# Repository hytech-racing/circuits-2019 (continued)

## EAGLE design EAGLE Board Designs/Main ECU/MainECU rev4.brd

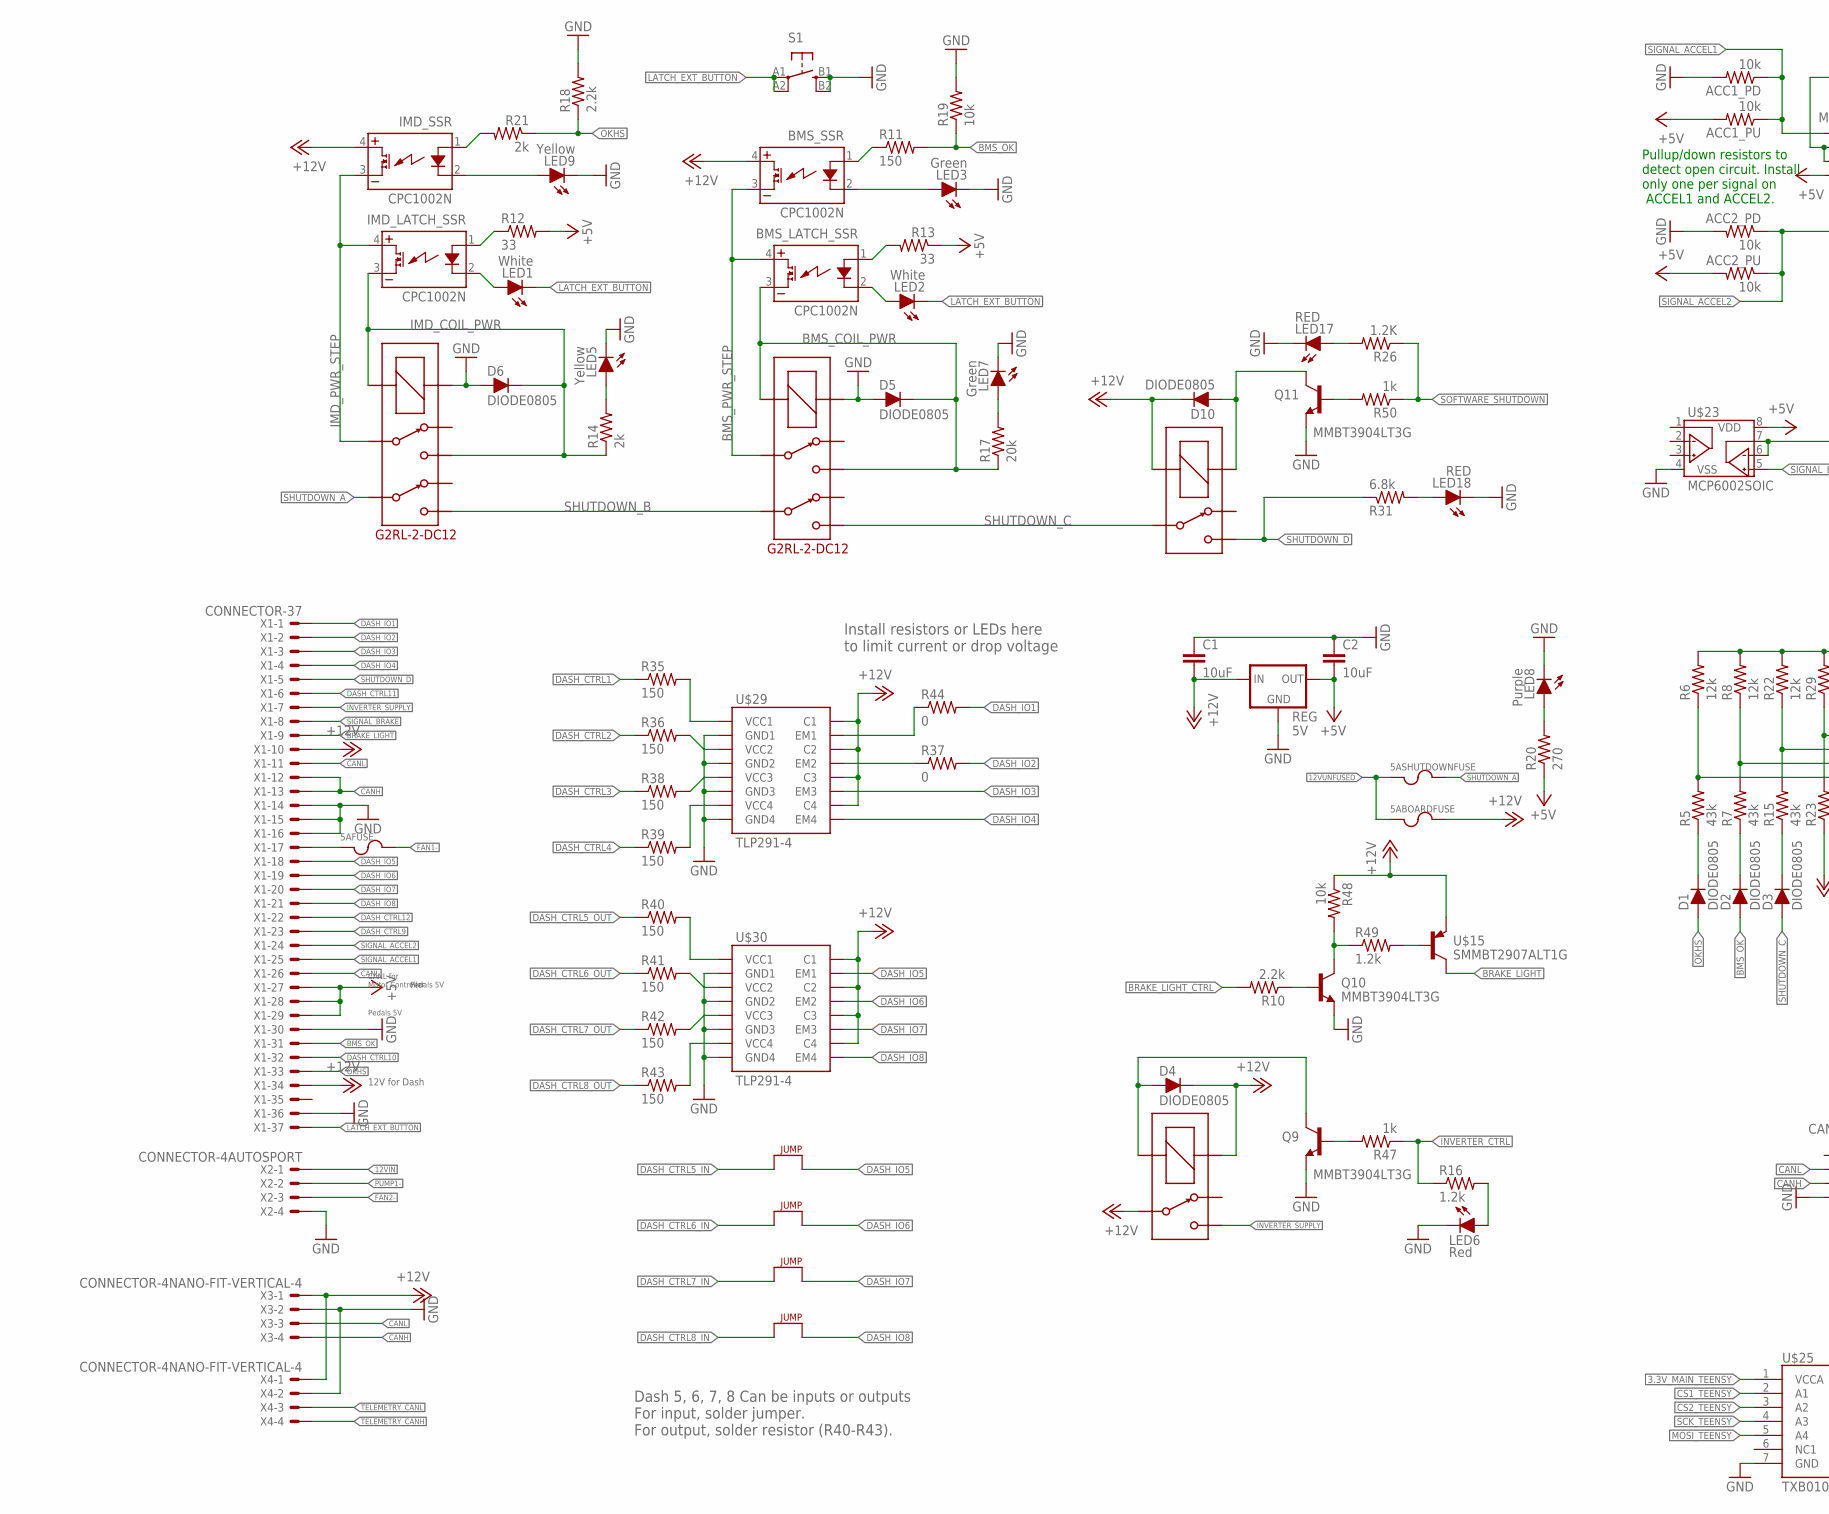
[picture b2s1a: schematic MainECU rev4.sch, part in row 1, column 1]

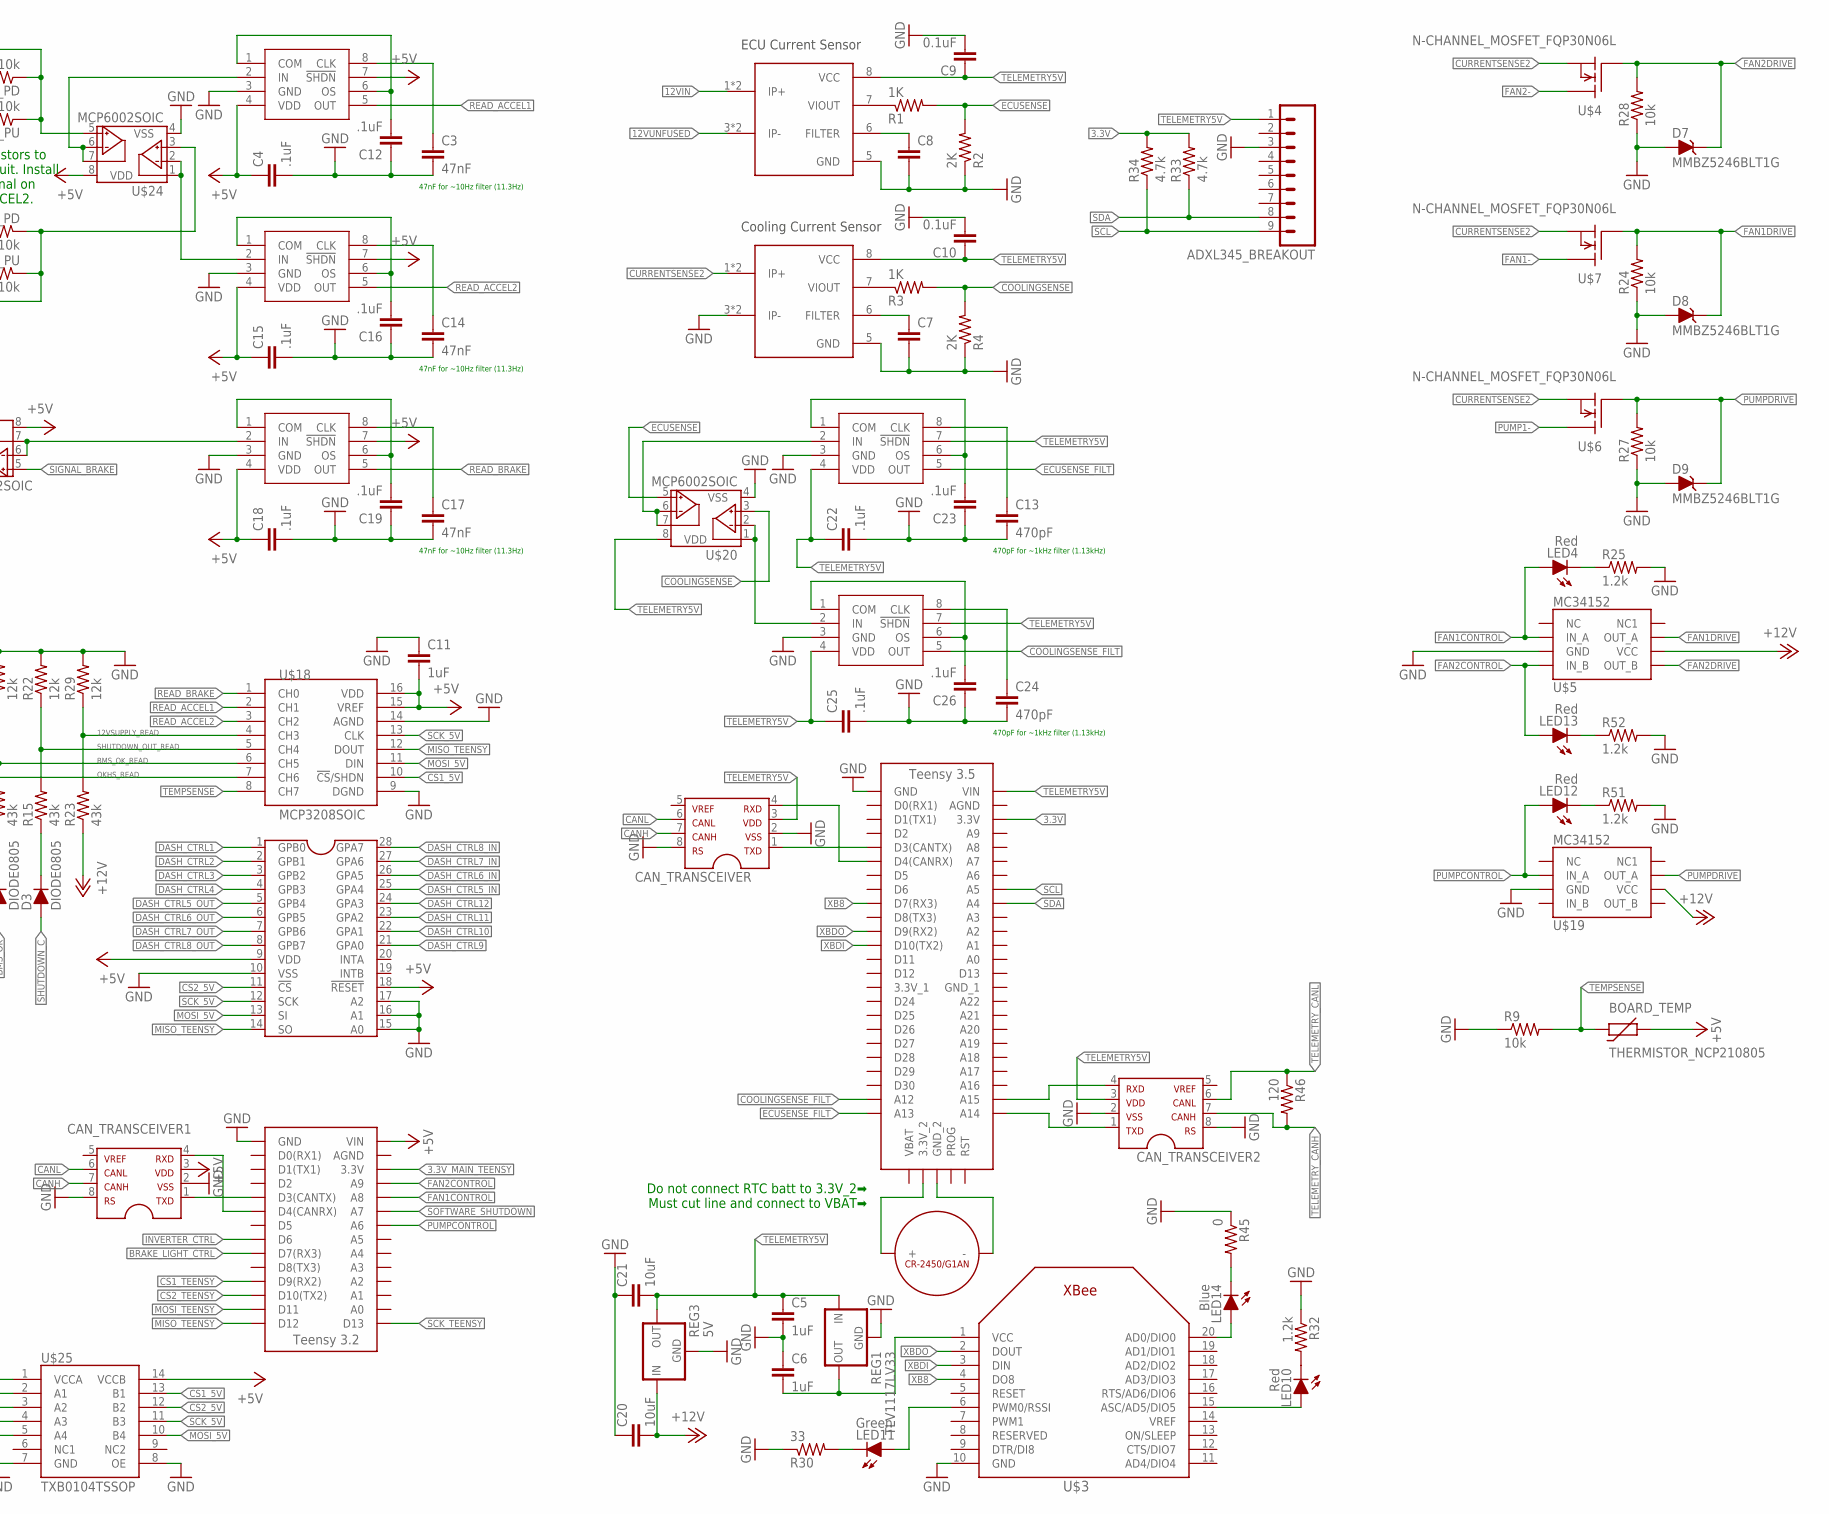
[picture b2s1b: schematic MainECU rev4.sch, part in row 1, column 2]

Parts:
5ABOARDFUSE, 5AFUSE, 5ASHUTDOWNFUSE: FUSE_MINIBLADE; MINI-BLADE_FUSE_HOLDER
ACC1_PD, ACC1_PU, ACC2_PD, ACC2_PU: 10k; 0805
ADXL345_BREAKOUT: M09; 1X09
BMS_LATCH_SSR: CPC1002N; SOP04
BMS_SSR: CPC1002N; SOP04
BOARD_TEMP: THERMISTOR_NCP210805; 0805
C1, C2, C20, C21: 10uF; 0805
C3, C14, C17: 47nF; 0805
C4, C12, C15, C16, C18, C19, C22, C23, C25, C26: .1uF; 0805
C5, C6, C11: 1uF; 0805
C7, C8: CAP0805; 0805
C9, C10: 0.1uF; 0805
C13, C24: 470pF; 0805
CAN_TRANSCEIVER, CAN_TRANSCEIVER1, CAN_TRANSCEIVER2: MCP2551; SOIC-08
D1, D2, D3, D4, D5, D6, D10: DIODE0805; 0805_D
D7, D8, D9: MMBZ5246BLT1G; SOT23
IMD_LATCH_SSR: CPC1002N; SOP04
IMD_SHUTDOWN, IMD_SHUTDOWN1: G2RL-2-DC12; G2RL-2
IMD_SSR: CPC1002N; SOP04
LED1, LED2: White; LED-805
LED3, LED7, LED11: Green; LED-805
LED4, LED6, LED10, LED12, LED13: Red; LED-805
LED5, LED9: Yellow; LED-805
LED8: Purple; LED-805
LED14: Blue; LED-805
LED17, LED18: RED; LED-805
Q9, Q10, Q11: MMBT3904LT3G; SOT23
R1, R3: 1K; 0805
R2, R4: 2K; 0805
R5, R7, R15, R23: 43k; 0805
R6, R8, R22, R29: 12k; 0805
R9, R19, R24, R27, R28, R48: 10k; 0805
R10, R18: 2.2k; 0805
R11, R35, R36, R38, R39, R40, R41, R42, R43: 150; 0805
R12, R13, R30: 33; 0805
R14, R21: 2k; 0805
R16, R25, R32, R49, R51, R52: 1.2k; 0805
R17: 20k; 0805
R20: 270; 0805
R26: 1.2K; 0805
R31: 6.8k; 0805
R33, R34: 4.7k; 0805
R37, R44, R45: 0; 0805
R46: 120; 0805
R47, R50: 1k; 0805
REG, REG3: 5V; OKI-78SR
REG1: TLV1117LV33; SOT223
S1: BTN_10-XXSMD; TACTILE_SWITCH_SMD_6.2MM_TALL
SOFTWARE_SHUTOFF: G5LE; ZF112
U$1: TEENSY_3.2_SIMPLE
U$2: TEENSY_3.5_EXT
U$3: XBEE
U$4, U$6, U$7: N-CHANNEL_MOSFET_FQP30N06L; TO-220-H-HOLE
U$5, U$19: MC34152; SOIC-08
U$8: G5LE; ZF112
U$9, U$10: ACS715_CURRENT_SENSOR; SOP8
U$11, U$12, U$13, U$14: JUMPER; 0805
U$15: SMMBT2907ALT1G; SOT23
U$16: CR-2450/G1AN
U$17: MCP23S17SSOP28; SSOP28
U$18: MCP3208SOIC; SOIC-16
U$20, U$23, U$24: MCP6002SOIC; SOIC-08
U$21, U$22, U$26, U$27, U$28: MAX7480; SOIC-08
U$25: TXB0104TSSOP; TSSOP-14
U$29, U$30: TLP291-4; 11-11F1
X1: CONNECTOR-37; AUTOSPORT_14-35
X2: CONNECTOR-4AUTOSPORT; AUTOSPORT_12-04
X3, X4: CONNECTOR-4NANO-FIT-VERTICAL-4; NANO-FIT_VERTICAL-4

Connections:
3.3V: R33.2, R34.2, U$2.3.3V
3.3V_MAIN_TEENSY: U$1.3.3V, U$25.1 (VCCA)
12VIN: U$9.1 (IP+), U$9.2 (IP+), X2.P$1
12VSUPPLY_READ: R23.2, R29.1, U$18.4 (CH3)
12VUNFUSED: 5ABOARDFUSE.L1 (1), 5ABOARDFUSE.L2 (1), 5ASHUTDOWNFUSE.L1 (1), 5ASHUTDOWNFUSE.L2 (1), U$9.3 (IP-), U$9.4 (IP-)
+5V: ACC1_PU.2, ACC2_PU.2, BOARD_TEMP.1, C2.2, C4.1, C11.2, C15.1, C18.1, CAN_TRANSCEIVER1.3, R12.2, R13.1, R20.1, REG.3 (OUT), U$1.VIN, U$17.9 (VDD), U$17.18 (!RESET), U$18.15 (VREF), U$18.16 (VDD), U$23.8 (VDD), U$24.8 (VDD), U$25.14 (VCCB), U$26.4 (VDD), U$26.7 (!SHDN), U$27.4 (VDD), U$27.7 (!SHDN), U$28.4 (VDD), U$28.7 (!SHDN), X1.P$27, X1.P$28, X1.P$29
+12V: 5ABOARDFUSE.R1 (2), 5ABOARDFUSE.R2 (2), BMS_SSR.4 (DC+), C1.2, C20.2, D4.C, D10.C, IMD_SSR.4 (DC+), R23.1, R48.1, REG.1 (IN), REG3.1 (IN), SOFTWARE_SHUTOFF.2 (COIL-), U$5.6 (VCC), U$8.1 (COIL+), U$8.P, U$15.2 (E), U$19.6 (VCC), U$29.10 (C4), U$29.12 (C3), U$29.14 (C2), U$29.16 (C1), U$30.10 (C4), U$30.12 (C3), U$30.14 (C2), U$30.16 (C1), X1.P$10, X1.P$34, X3.P$1, X4.P$1
BMS_COIL_PWR: BMS_LATCH_SSR.3 (DC-), D5.C, IMD_SHUTDOWN1.4, IMD_SHUTDOWN1.COIL-, R17.1
BMS_OK: D2.A, R11.2, R19.1, X1.P$31
BMS_OK_READ: R7.2, R8.1, U$18.6 (CH5)
BMS_PWR_STEP: BMS_LATCH_SSR.4 (DC+), BMS_SSR.3 (DC-), IMD_SHUTDOWN1.3
BRAKE_LIGHT: U$15.3 (C), X1.P$9
BRAKE_LIGHT_CTRL: R10.2, U$1.D7(RX3)
CANH: CAN_TRANSCEIVER.7, CAN_TRANSCEIVER1.7, X1.P$12, X1.P$13, X3.P$4
CANL: CAN_TRANSCEIVER.6, CAN_TRANSCEIVER1.6, X1.P$11, X1.P$26, X3.P$3
COOLINGSENSE: R3.2, R4.2, U$20.3 (VINA+)
COOLINGSENSE_FILT: U$2.A12, U$22.5 (OUT)
CS1_5V: U$18.10 (!CS!/SHDN), U$25.13 (B1)
CS1_TEENSY: U$1.D9(RX2), U$25.2 (A1)
CS2_5V: U$17.11 (!CS), U$25.12 (B2)
CS2_TEENSY: U$1.D10(TX2), U$25.3 (A2)
CURRENTSENSE2: U$4.3 (S), U$6.3 (S), U$7.3 (S), U$10.1 (IP+), U$10.2 (IP+)
DASH_CTRL1: R35.1, U$17.1 (GPB0)
DASH_CTRL2: R36.1, U$17.2 (GPB1)
DASH_CTRL3: R38.1, U$17.3 (GPB2)
DASH_CTRL4: R39.1, U$17.4 (GPB3)
DASH_CTRL5_IN: U$12.2, U$17.25 (GPA4)
DASH_CTRL5_OUT: R40.1, U$17.5 (GPB4)
DASH_CTRL6_IN: U$11.2, U$17.26 (GPA5)
DASH_CTRL6_OUT: R41.1, U$17.6 (GPB5)
DASH_CTRL7_IN: U$13.2, U$17.27 (GPA6)
DASH_CTRL7_OUT: R42.1, U$17.7 (GPB6)
DASH_CTRL8_IN: U$14.2, U$17.28 (GPA7)
DASH_CTRL8_OUT: R43.1, U$17.8 (GPB7)
DASH_CTRL9: U$17.21 (GPA0), X1.P$23
DASH_CTRL10: U$17.22 (GPA1), X1.P$32
DASH_CTRL11: U$17.23 (GPA2), X1.P$6
DASH_CTRL12: U$17.24 (GPA3), X1.P$22
DASH_IO1: R44.2, X1.P$1
DASH_IO2: R37.2, X1.P$2
DASH_IO3: U$29.11 (EM3), X1.P$3
DASH_IO4: U$29.9 (EM4), X1.P$4
DASH_IO5: U$12.1, U$30.15 (EM1), X1.P$18
DASH_IO6: U$11.1, U$30.13 (EM2), X1.P$19
DASH_IO7: U$13.1, U$30.11 (EM3), X1.P$20
DASH_IO8: U$14.1, U$30.9 (EM4), X1.P$21
ECUSENSE: R1.2, R2.2, U$20.5 (VINB+)
ECUSENSE_FILT: U$2.A13, U$21.5 (OUT)
FAN1-: 5AFUSE.R1 (2), 5AFUSE.R2 (2), U$7.2 (D)
FAN1CONTROL: LED4.A, U$1.A8, U$5.2 (IN_A)
FAN1DRIVE: D8.3 (C), R24.2, U$5.7 (OUT_A), U$7.1 (G)
FAN2-: U$4.2 (D), X2.P$3
FAN2CONTROL: LED13.A, U$1.A9, U$5.4 (IN_B)
FAN2DRIVE: D7.3 (C), R28.2, U$4.1 (G), U$5.5 (OUT_B)
GND: ACC1_PD.2, ACC2_PD.2, ADXL345_BREAKOUT.3, C1.1, C2.1, C3.2, C4.2, C5.2, C6.1, C7.2, C8.2, C9.2, C10.2, C11.1, C12.1, C13.2, C14.2, C15.2, C16.1, C17.2, C18.2, C19.1, C20.1, C21.1, C22.2, C23.1, C24.2, C25.2, C26.1, CAN_TRANSCEIVER.2, CAN_TRANSCEIVER.8, CAN_TRANSCEIVER1.2, CAN_TRANSCEIVER1.8, CAN_TRANSCEIVER2.2, CAN_TRANSCEIVER2.8, D5.A, D6.A, D7.1 (A), D8.1 (A), D9.1 (A), IMD_SHUTDOWN.COIL+, IMD_SHUTDOWN1.COIL+, LED3.C, LED5.C, LED6.C, LED7.C, LED8.C, LED9.C, LED17.C, LED18.C, Q9.2 (EMITTER), Q10.2 (EMITTER), Q11.2 (EMITTER), R2.1, R4.1, R6.2, R8.2, R9.1, R18.2, R19.2, R22.2, R24.1, R25.2, R27.1, R28.1, R29.2, R30.1, R32.1, R45.1, R51.2, R52.2, REG.2 (GND), REG1.1 (GND), REG3.2 (GND), S1.B1 (S), S1.B2 (S1), U$1.GND, U$2.GND, U$3.10 (GND), U$5.3 (GND), U$9.5 (GND), U$10.3 (IP-), U$10.4 (IP-), U$10.5 (GND), U$17.10 (VSS), U$17.15 (A0), U$17.16 (A1), U$17.17 (A2), U$18.9 (DGND), U$18.14 (AGND), U$19.3 (GND), U$20.4 (VSS), U$21.3 (GND), U$22.3 (GND), U$23.4 (VSS), U$24.4 (VSS), U$25.7 (GND), U$25.8 (OE), U$26.3 (GND), U$27.3 (GND), U$28.3 (GND), U$29.2 (GND1), U$29.4 (GND2), U$29.6 (GND3), U$29.8 (GND4), U$30.2 (GND1), U$30.4 (GND2), U$30.6 (GND3), U$30.8 (GND4), X1.P$14, X1.P$15, X1.P$16, X1.P$30, X1.P$36, X2.P$4, X3.P$2, X4.P$2
IMD_COIL_PWR: D6.C, IMD_LATCH_SSR.3 (DC-), IMD_SHUTDOWN.4, IMD_SHUTDOWN.COIL-, R14.1
IMD_PWR_STEP: IMD_LATCH_SSR.4 (DC+), IMD_SHUTDOWN.3, IMD_SSR.3 (DC-)
INVERTER_CTRL: R16.1, R47.1, U$1.D6
INVERTER_SUPPLY: U$8.S, X1.P$7
LATCH_EXT_BUTTON: LED1.C, LED2.C, S1.A1, S1.A2 (P1), X1.P$37
MISO_TEENSY: U$1.D12, U$17.14 (SO), U$18.12 (DOUT)
MOSI_5V: U$17.13 (SI), U$18.11 (DIN), U$25.10 (B4)
MOSI_TEENSY: U$1.D11, U$25.5 (A4)
unnamed: 5AFUSE.L1 (1), 5AFUSE.L2 (1), X1.P$17
unnamed: IMD_LATCH_SSR.2 (CONTROL-), LED1.A
unnamed: R1.1, U$9.7 (VIOUT)
unnamed: C12.2, U$27.1 (COM), U$27.6 (OS)
unnamed: IMD_LATCH_SSR.1 (CONTROL+), R12.1
unnamed: R3.1, U$10.7 (VIOUT)
unnamed: Q10.1 (BASE), R10.1
unnamed: C8.1, U$9.6 (FILTER)
unnamed: BMS_SSR.2 (CONTROL-), LED3.A
unnamed: D1.C, R5.1
unnamed: D2.C, R7.1
unnamed: BMS_LATCH_SSR.1 (CONTROL+), R13.2
unnamed: CAN_TRANSCEIVER.4, U$2.D4(CANRX)
unnamed: CAN_TRANSCEIVER.1, U$2.D3(CANTX)
unnamed: CAN_TRANSCEIVER1.4, U$1.D4(CANRX)
unnamed: BMS_LATCH_SSR.2 (CONTROL-), LED2.A
unnamed: Q10.3 (COLLECTOR), R48.2, R49.1
unnamed: BMS_SSR.1 (CONTROL+), R11.1
unnamed: LED5.A, R14.2
unnamed: U$20.1 (VOUTA), U$20.2 (VINA-), U$22.2 (IN)
unnamed: C3.1, U$27.8 (CLK)
unnamed: CAN_TRANSCEIVER1.1, U$1.D3(CANTX)
unnamed: U$24.1 (VOUTA), U$24.2 (VINA-), U$28.2 (IN)
unnamed: U$24.6 (VINB-), U$24.7 (VOUTB), U$27.2 (IN)
unnamed: U$23.6 (VINB-), U$23.7 (VOUTB), U$26.2 (IN)
unnamed: Q11.1 (BASE), R50.2
unnamed: D10.A, Q11.3 (COLLECTOR), SOFTWARE_SHUTOFF.1 (COIL+)
unnamed: LED6.A, R16.2
unnamed: LED8.A, R20.2
unnamed: R36.2, U$29.3 (VCC2)
unnamed: IMD_SSR.1 (CONTROL+), R21.2
unnamed: LED7.A, R17.2
unnamed: D3.C, R15.1
unnamed: IMD_SSR.2 (CONTROL-), LED9.A
unnamed: LED14.C, R45.2
unnamed: C16.2, U$28.1 (COM), U$28.6 (OS)
unnamed: C19.2, U$26.1 (COM), U$26.6 (OS)
unnamed: C14.1, U$28.8 (CLK)
unnamed: U$20.6 (VINB-), U$20.7 (VOUTB), U$21.2 (IN)
unnamed: LED18.A, R31.2
unnamed: C17.1, U$26.8 (CLK)
unnamed: R37.1, U$29.13 (EM2)
unnamed: C23.2, U$21.1 (COM), U$21.6 (OS)
unnamed: C13.1, U$21.8 (CLK)
unnamed: LED11.C, R30.2
unnamed: LED17.A, R26.2
unnamed: LED11.A, U$3.6 (PWM0/RSSI)
unnamed: C7.1, U$10.6 (FILTER)
unnamed: LED10.A, U$3.15 (ASC/AD5/DIO5)
unnamed: LED10.C, R32.2
unnamed: R35.2, U$29.1 (VCC1)
unnamed: R38.2, U$29.5 (VCC3)
unnamed: R39.2, U$29.7 (VCC4)
unnamed: R40.2, U$30.1 (VCC1)
unnamed: R41.2, U$30.3 (VCC2)
unnamed: R42.2, U$30.5 (VCC3)
unnamed: R43.2, U$30.7 (VCC4)
unnamed: R49.2, U$15.1 (B)
unnamed: R44.1, U$29.15 (EM1)
unnamed: U$2.3.3V_2, U$16.+_0 (+), U$16.+_1 (+)
unnamed: U$2.GND_2, U$16.-
unnamed: CAN_TRANSCEIVER2.4, U$2.A15
unnamed: LED14.A, U$3.20 (AD0/DIO0)
unnamed: CAN_TRANSCEIVER2.1, U$2.A14
unnamed: Q9.1 (BASE), R47.2
unnamed: D4.A, Q9.3 (COLLECTOR), U$8.2 (COIL-)
unnamed: C26.2, U$22.1 (COM), U$22.6 (OS)
unnamed: C24.1, U$22.8 (CLK)
unnamed: LED4.C, R25.1
unnamed: LED12.C, R51.1
unnamed: LED13.C, R52.1
OKHS: D1.A, R18.1, R21.1, X1.P$33
OKHS_READ: R5.2, R6.1, U$18.7 (CH6)
PUMP1-: U$6.2 (D), X2.P$2
PUMPCONTROL: LED12.A, U$1.A6, U$19.2 (IN_A)
PUMPDRIVE: D9.3 (C), R27.2, U$6.1 (G), U$19.7 (OUT_A)
READ_ACCEL1: U$18.2 (CH1), U$27.5 (OUT)
READ_ACCEL2: U$18.3 (CH2), U$28.5 (OUT)
READ_BRAKE: U$18.1 (CH0), U$26.5 (OUT)
SCK_5V: U$17.12 (SCK), U$18.13 (CLK), U$25.11 (B3)
SCK_TEENSY: U$1.D13, U$25.4 (A3)
SCL: ADXL345_BREAKOUT.9, R34.1, U$2.A5
SDA: ADXL345_BREAKOUT.8, R33.1, U$2.A4
SHUTDOWN_A: 5ASHUTDOWNFUSE.R1 (2), 5ASHUTDOWNFUSE.R2 (2), IMD_SHUTDOWN.6
SHUTDOWN_B: IMD_SHUTDOWN.5, IMD_SHUTDOWN1.6
SHUTDOWN_C: D3.A, IMD_SHUTDOWN1.5, SOFTWARE_SHUTOFF.P
SHUTDOWN_D: R31.1, SOFTWARE_SHUTOFF.S, X1.P$5
SHUTDOWN_OUT_READ: R15.2, R22.1, U$18.5 (CH4)
SIGNAL_ACCEL1: ACC1_PD.1, ACC1_PU.1, U$24.5 (VINB+), X1.P$25
SIGNAL_ACCEL2: ACC2_PD.1, ACC2_PU.1, U$24.3 (VINA+), X1.P$24
SIGNAL_BRAKE: U$23.5 (VINB+), X1.P$8
SOFTWARE_SHUTDOWN: R26.1, R50.1, U$1.A7
TELEMETRY5V: ADXL345_BREAKOUT.1, C5.1, C9.1, C10.1, C21.2, C22.1, C25.1, CAN_TRANSCEIVER.3, CAN_TRANSCEIVER2.3, REG1.3 (IN), REG3.3 (OUT), U$2.VIN, U$9.8 (VCC), U$10.8 (VCC), U$20.8 (VDD), U$21.4 (VDD), U$21.7 (!SHDN), U$22.4 (VDD), U$22.7 (!SHDN)
TELEMETRY_CANH: CAN_TRANSCEIVER2.7, R46.2, X4.P$4
TELEMETRY_CANL: CAN_TRANSCEIVER2.6, R46.1, X4.P$3
TEMPSENSE: BOARD_TEMP.2, R9.2, U$18.8 (CH7)
VCC: C6.2, REG1.2 (OUT), REG1.4 (OUT), U$3.1 (VCC)
XB8: U$2.D7(RX3), U$3.4 (DO8)
XBDI: U$2.D10(TX2), U$3.3 (DIN)
XBDO: U$2.D9(RX2), U$3.2 (DOUT)

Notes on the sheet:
ECU Current Sensor
Cooling Current Sensor
Pullup/down resistors to detect open circuit. Install only one per signal on ACCEL1 and ACCEL2.
Pedals 5V
CANL for Motor Controller
47nF for ~10Hz filter (11.3Hz)
12V for Dash
Dash 5, 6, 7, 8 Can be inputs or outputs For input, solder jumper. For output, solder resistor (R40-R43).
470pF for ~1kHz filter (1.13kHz)
Install resistors or LEDs here to limit current or drop voltage
Do not connect RTC batt to 3.3V_2➡ Must cut line and connect to VBAT➡

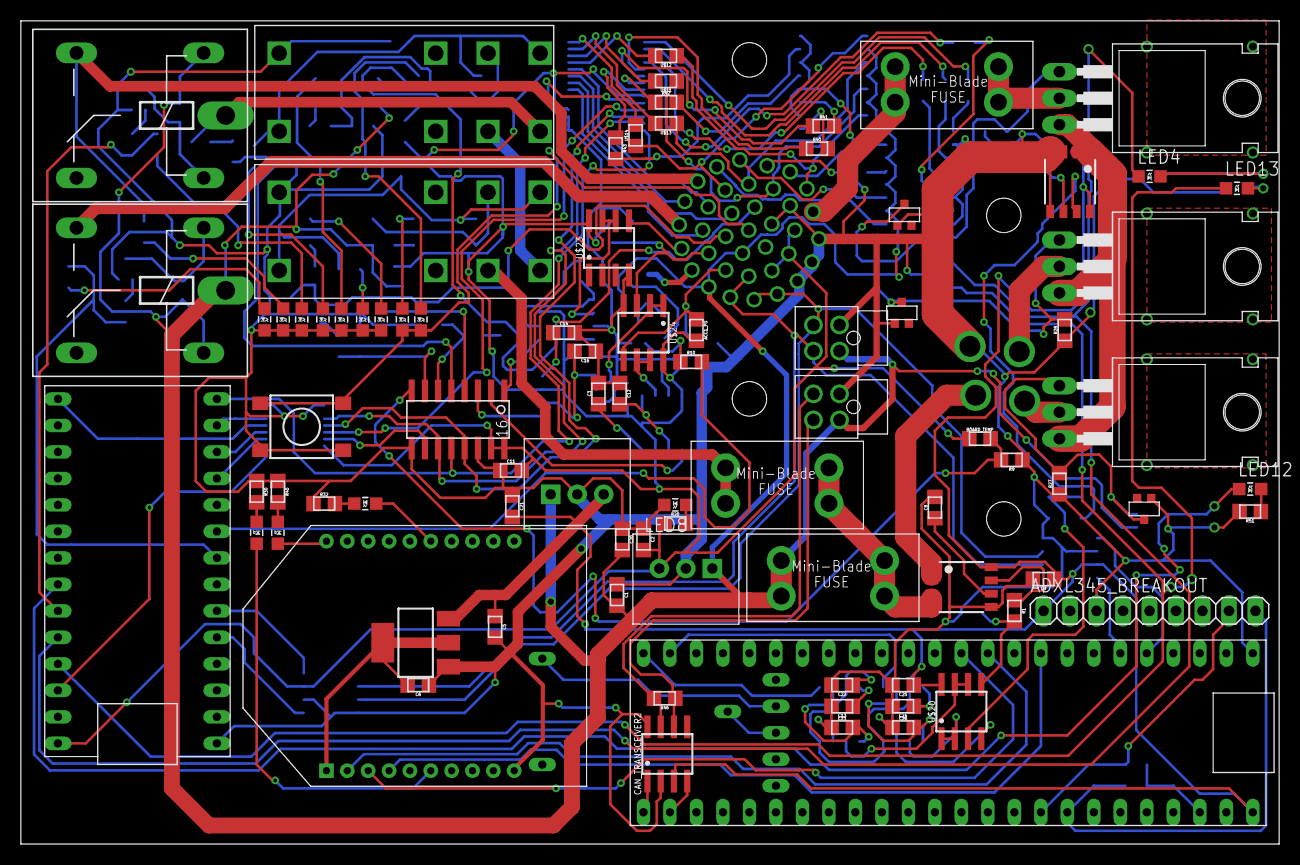
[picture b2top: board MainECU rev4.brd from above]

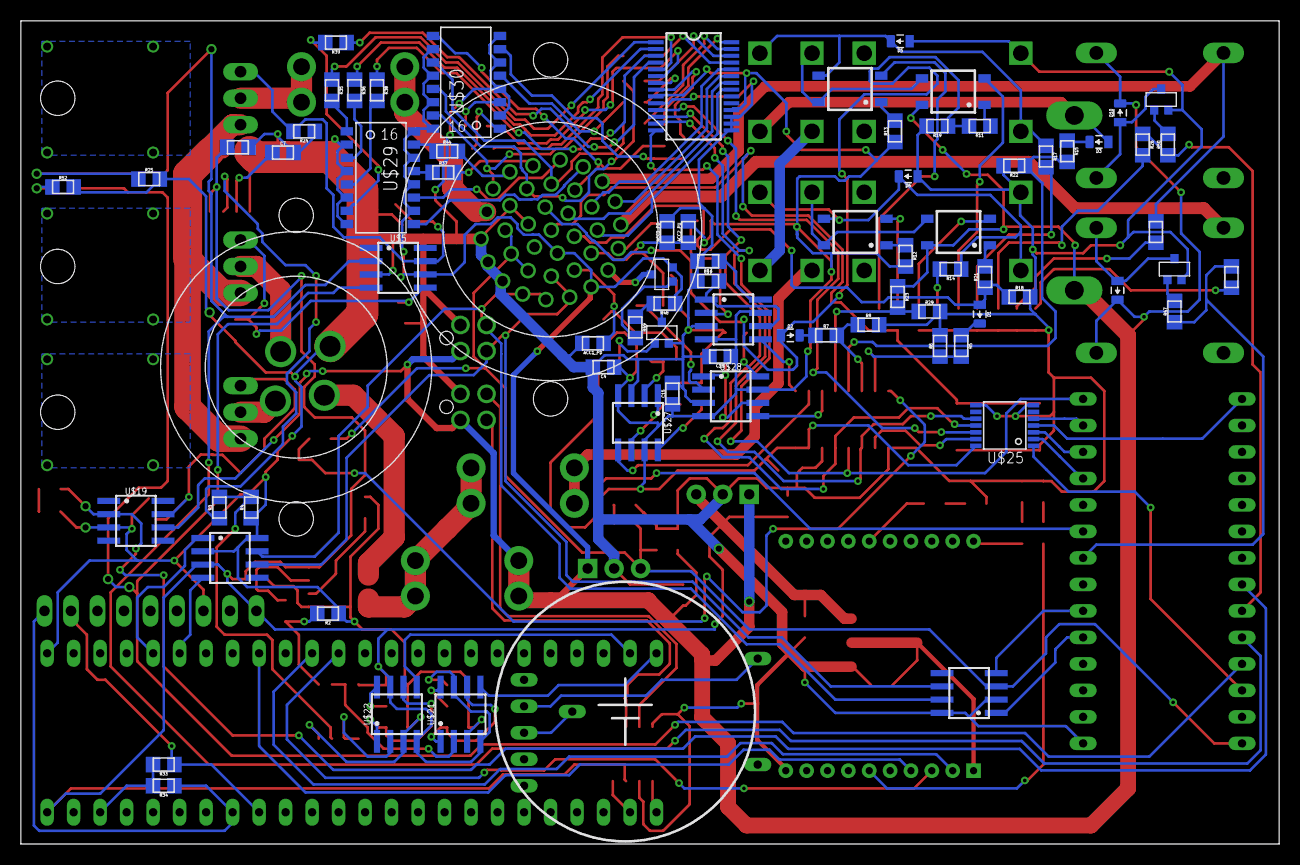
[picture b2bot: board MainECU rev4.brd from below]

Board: 2 copper layers, 120.6 x 78.9 mm, 164 parts (78 on the bottom side), 163 nets.

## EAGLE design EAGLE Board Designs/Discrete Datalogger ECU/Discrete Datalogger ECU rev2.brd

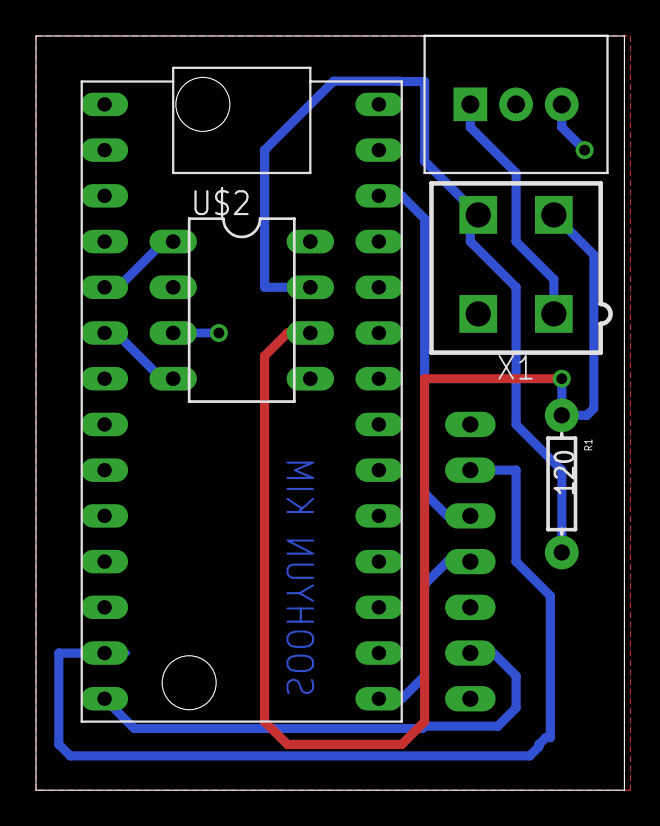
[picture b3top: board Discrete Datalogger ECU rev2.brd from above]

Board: 2 copper layers, 32.7 x 41.9 mm, 6 parts (0 on the bottom side), 11 nets.

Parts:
IC1: TO-220
R1: 120; AXIAL-0.3
U$1: TEENSY_3.2_SIMPLE
U$2: MCP2551DIL; DIL08
U$3: SDCARD_INTERFACE
X1: CONNECTOR-4; MINIFIT_5566-4

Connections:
12V: IC1.1, X1.1
CANH: R1.P$2, U$2.7, X1.4
CANL: R1.P$1, U$2.6, X1.3
GND: IC1.2, U$1.GND, U$2.2, U$2.8, U$3.CS, U$3.GND, X1.2
unnamed: U$1.D3(CANTX), U$2.1
unnamed: U$1.D4(CANRX), U$2.4
unnamed: U$1.D13, U$3.SCK
unnamed: U$1.D11, U$3.DI
unnamed: U$1.3.3V, U$3.VCC
unnamed: U$1.D12, U$3.DO
VIN: IC1.3, U$1.VIN, U$2.3

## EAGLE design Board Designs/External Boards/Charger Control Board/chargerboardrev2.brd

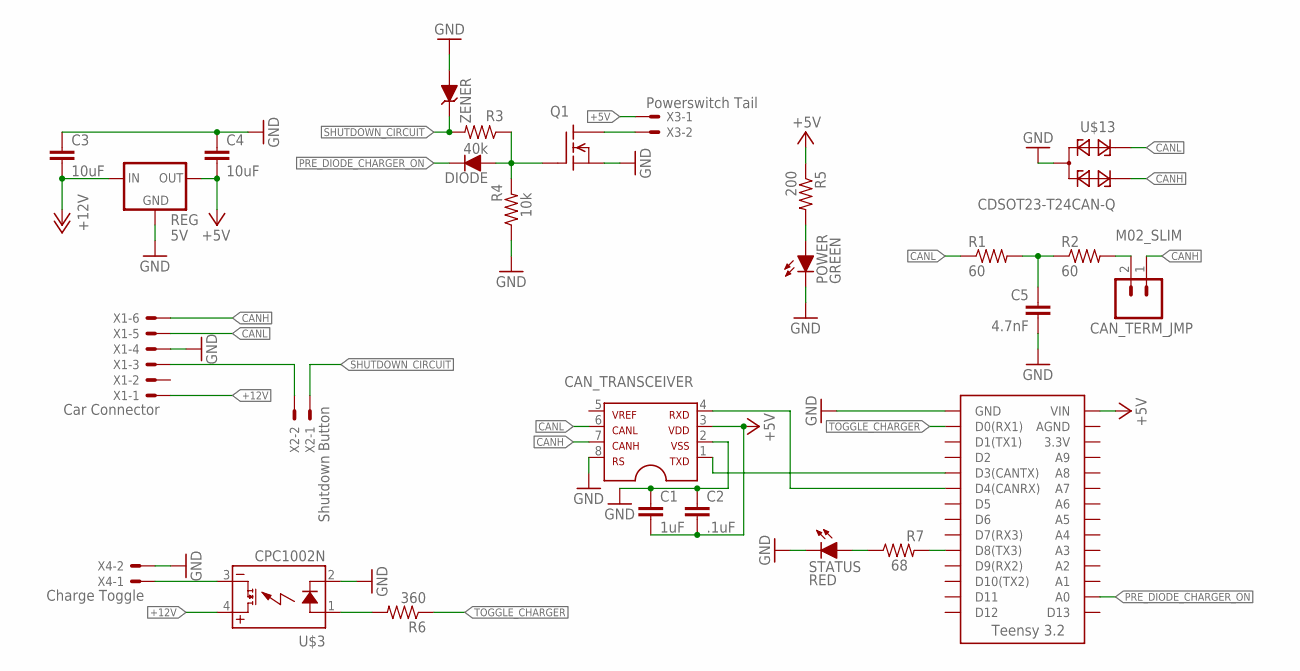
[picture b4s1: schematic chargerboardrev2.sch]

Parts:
C1: 1uF; 0805
C2: .1uF; 0805
C3, C4: 10uF; 0805
C5: 4.7nF; 0805
CAN_TERM_JMP: M02_SLIM; 1X02_SLIM
CAN_TRANSCEIVER: MCP2551; SOIC-08
POWER: GREEN; LED-805
Q1: DMG3406LSOT; SOT23
R1, R2: 60; 0805
R3: 40k; 0805
R4: 10k; 0805
R5: 200; 0805
R6: 360; 0805
R7: 68; 0805
REG: 5V; OKI-78SR
STATUS: RED; LED-805
U$3: CPC1002N; SOP04
U$4: TEENSY_3.2_SIMPLE
U$13: CDSOT23-T24CAN-Q; SOT23
X1: Car Connector; NANO-FIT_VERTICAL-6
X2: Shutdown Button; MINIFIT_5566-2
X3: Powerswitch Tail; MINIFIT_5566-2
X4: Charge Toggle; MINIFIT_5566-2
ZENER: DIODE_ZENER; SOT23
ZENER1: DIODE; 0805_D

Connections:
+5V: C1.2, C2.2, C4.2, CAN_TRANSCEIVER.3, R5.1, REG.3 (OUT), U$4.VIN, X3.1
+12V: C3.2, REG.1 (IN), U$3.4 (DC+), X1.P$1
CANH: CAN_TERM_JMP.1, CAN_TRANSCEIVER.7, U$13.2, X1.P$6
CANL: CAN_TRANSCEIVER.6, R1.1, U$13.1, X1.P$5
CHARGER_ON: Q1.1 (G), R3.1, R4.2, ZENER1.A; also elsewhere on the board
GND: C1.1, C2.1, C3.1, C4.1, C5.2, CAN_TRANSCEIVER.2, CAN_TRANSCEIVER.8, POWER.C, Q1.2 (S), R4.1, REG.2 (GND), STATUS.C, U$3.2 (CONTROL-), U$4.GND, U$13.3, X1.P$4, X4.2, ZENER.1 (A)
unnamed: Q1.3 (D), X3.2
unnamed: U$3.3 (DC-), X4.1
unnamed: R7.1, STATUS.A
unnamed: POWER.A, R5.2
unnamed: R6.2, U$3.1 (CONTROL+)
unnamed: R7.2, U$4.D8(TX3)
unnamed: CAN_TRANSCEIVER.4, U$4.D4(CANRX)
unnamed: CAN_TERM_JMP.2, R2.2
unnamed: CAN_TRANSCEIVER.1, U$4.D3(CANTX)
unnamed: C5.1, R1.2, R2.1
PRE_BRB_SHUTDOWN_CIRCUIT: X1.P$3, X2.2
PRE_DIODE_CHARGER_ON: U$4.A0, ZENER1.C; also elsewhere on the board
SHUTDOWN_CIRCUIT: R3.2, X2.1, ZENER.3 (C)
TOGGLE_CHARGER: R6.1, U$4.D0(RX1)

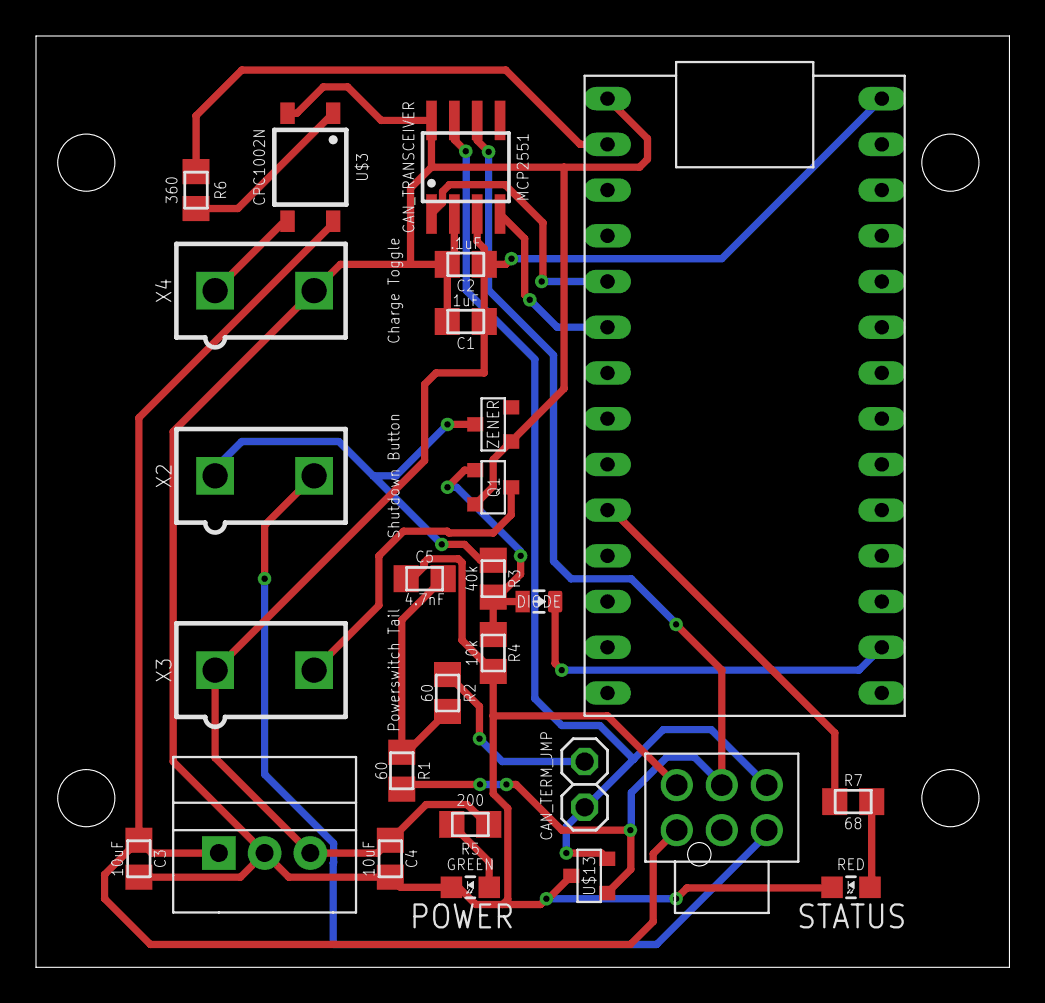
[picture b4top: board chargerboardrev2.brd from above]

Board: 4 copper layers, 54.1 x 51.7 mm, 27 parts (0 on the bottom side), 20 nets.

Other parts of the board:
DIODE: DIODE; 0805_D

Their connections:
CHARGER_ON: DIODE.A; also elsewhere on the board
PRE_DIODE_CHARGER_ON: DIODE.C; also elsewhere on the board

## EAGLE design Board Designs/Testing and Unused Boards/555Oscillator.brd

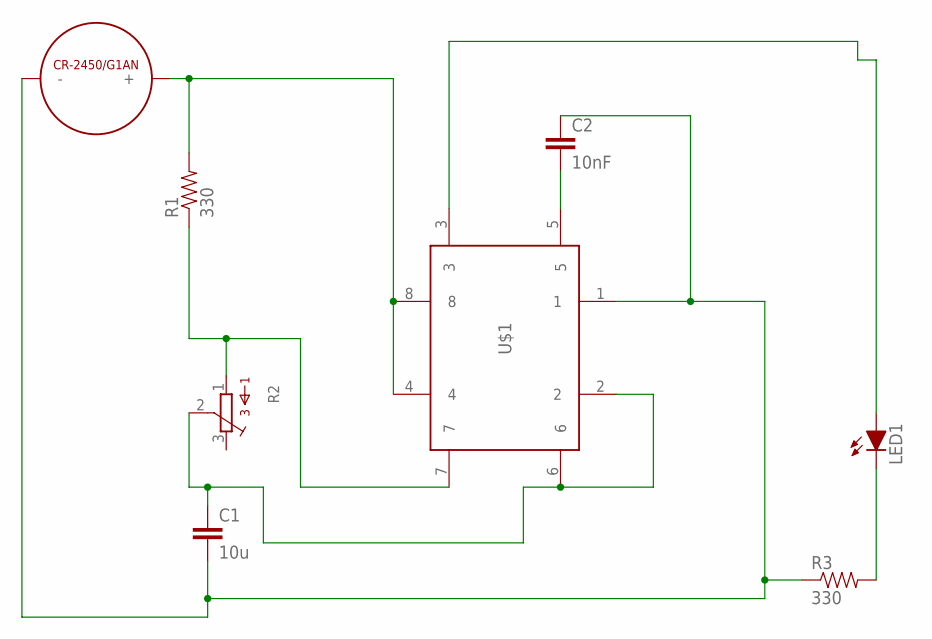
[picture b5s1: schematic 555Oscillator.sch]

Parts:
C1: 10u; AXIAL-5MM
C2: 10nF; AXIAL-5MM
LED1: LED-5MM
R1, R3: 330; AXIAL-0.3
R2: TRIMPOT_3296C; TRIMPOT_3296
U$1: 555_TIMER; DIL08
U$2: CR-2450/G1AN

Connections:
unnamed: C1.P$2 (2), C2.P$1 (1), R3.P$1 (1), U$1.1, U$2.-
unnamed: R1.P$1 (1), R2.1, U$1.7
unnamed: R1.P$2 (2), U$1.4, U$1.8, U$2.+_0 (+), U$2.+_1 (+)
unnamed: LED1.A, U$1.3
unnamed: LED1.K (C), R3.P$2 (2)
unnamed: C2.P$2 (2), U$1.5
unnamed: C1.P$1 (1), R2.2, U$1.2, U$1.6

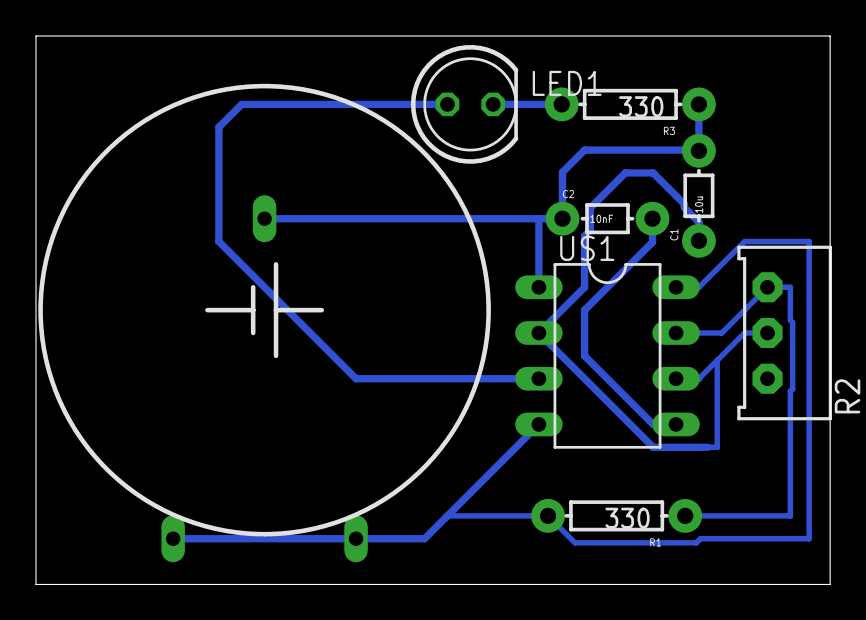
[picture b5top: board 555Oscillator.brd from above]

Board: 2 copper layers, 44.1 x 30.5 mm, 8 parts (0 on the bottom side), 7 nets.

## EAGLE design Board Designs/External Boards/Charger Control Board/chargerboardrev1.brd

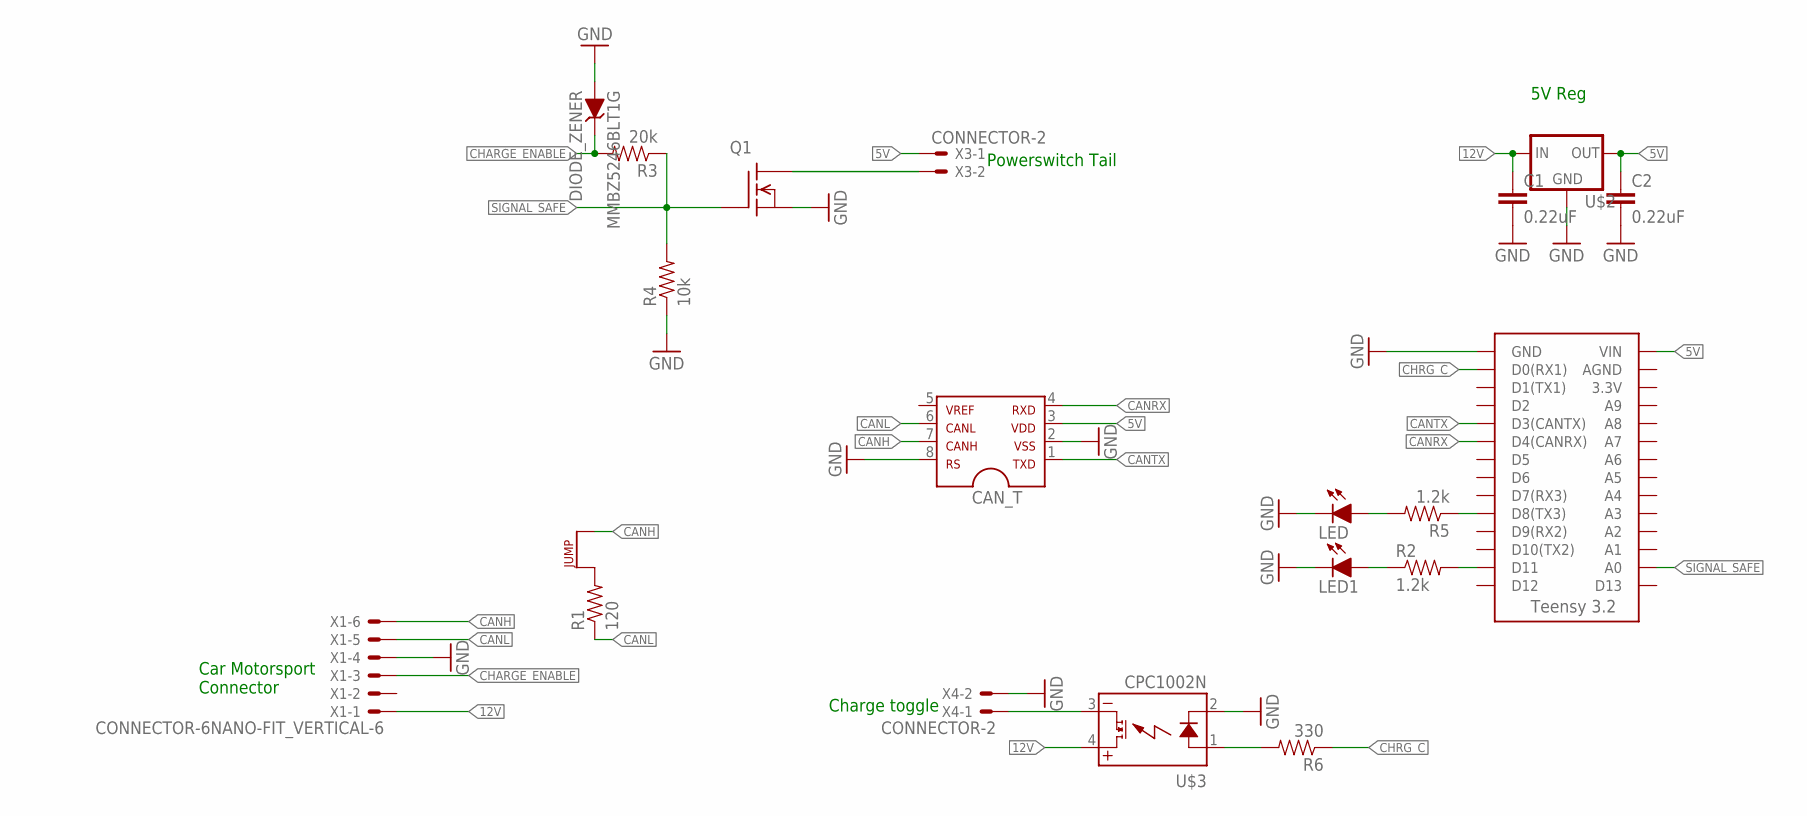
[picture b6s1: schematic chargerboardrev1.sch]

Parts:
C1, C2: 0.22uF; 0805
CAN_T: MCP2551; SOIC-08
J1: JUMPER.1; 1X02
LED, LED1: LED-0805; LED-805
MMBZ5246BLT1G: DIODE_ZENER; SOT23
Q1: DMG3406LSOT; SOT23
R1: 120; 0805
R2, R5: 1.2k; 0805
R3: 20k; 0805
R4: 10k; 0805
R6: 330; 0805
U$1: TEENSY_3.2_SIMPLE
U$2: 5VREG_LM340-NLM340MPX-5.0/NOPB; SOT223
U$3: CPC1002N; SOP04
X1: CONNECTOR-6NANO-FIT_VERTICAL-6; NANO-FIT_VERTICAL-6
X3, X4: CONNECTOR-2; MINIFIT_5566-2

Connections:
5V: C2.1, CAN_T.3, U$1.VIN, U$2.3 (OUT), X3.1
12V: C1.1, U$2.1 (IN), U$3.4 (DC+), X1.P$1
CANH: CAN_T.7, J1.2, X1.P$6
CANL: CAN_T.6, R1.1, X1.P$5
CANRX: CAN_T.4, U$1.D4(CANRX)
CANTX: CAN_T.1, U$1.D3(CANTX)
CHARGE_ENABLE: MMBZ5246BLT1G.3 (C), R3.2, X1.P$3
CHRG_C: R6.1, U$1.D0(RX1)
GND: C1.2, C2.2, CAN_T.2, CAN_T.8, LED.C, LED1.C, MMBZ5246BLT1G.1 (A), Q1.2 (S), R4.1, U$1.GND, U$2.2 (GND), U$2.4 (GND), U$3.2 (CONTROL-), X1.P$4, X4.2
unnamed: Q1.3 (D), X3.2
unnamed: R2.2, U$1.D11
unnamed: R5.1, U$1.D8(TX3)
unnamed: LED1.A, R2.1
unnamed: J1.1, R1.2
unnamed: LED.A, R5.2
unnamed: U$3.3 (DC-), X4.1
unnamed: R6.2, U$3.1 (CONTROL+)
SIGNAL_SAFE: Q1.1 (G), R3.1, R4.2, U$1.A0

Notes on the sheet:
Car Motorsport Connector
Powerswitch Tail
Charge toggle
5V Reg

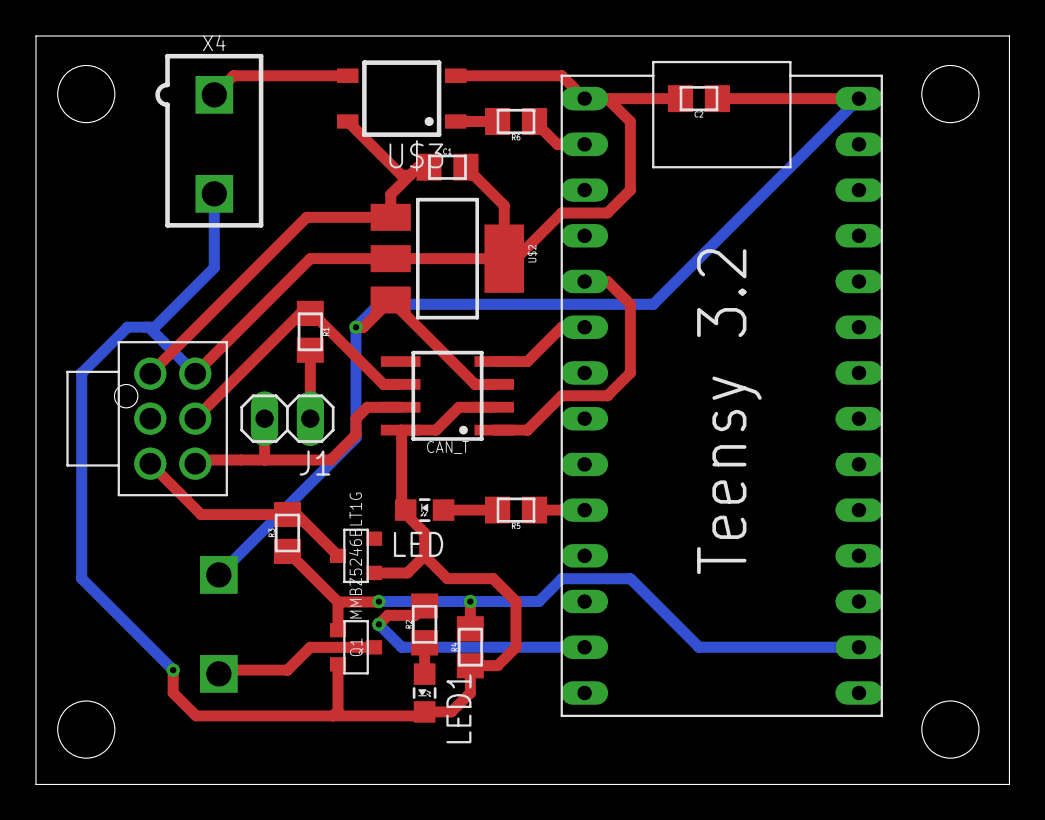
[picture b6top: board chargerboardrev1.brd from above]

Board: 2 copper layers, 54.1 x 41.6 mm, 20 parts (1 on the bottom side), 18 nets.
